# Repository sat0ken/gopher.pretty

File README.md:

# gopher.pretty

Gopher kicad Footprint Library.
Let's make your own Gopher Board, and enjoy tinygo!

## Usage

1. clone this repository to your pc.
2. Add the cloned folder to the footprint library path of kicad.
3. make your own board!

You can also use this as is.

I have confirmed that the project can be opened using kicad 8.0.

The Kicad project I created can be found in the following repository.

[https://github.com/sat0ken/gopher-board](https://github.com/sat0ken/gopher-board)

## Thanks

The Go gopher was designed by Renee French.
[http://reneefrench.blogspot.com/](http://reneefrench.blogspot.com/)

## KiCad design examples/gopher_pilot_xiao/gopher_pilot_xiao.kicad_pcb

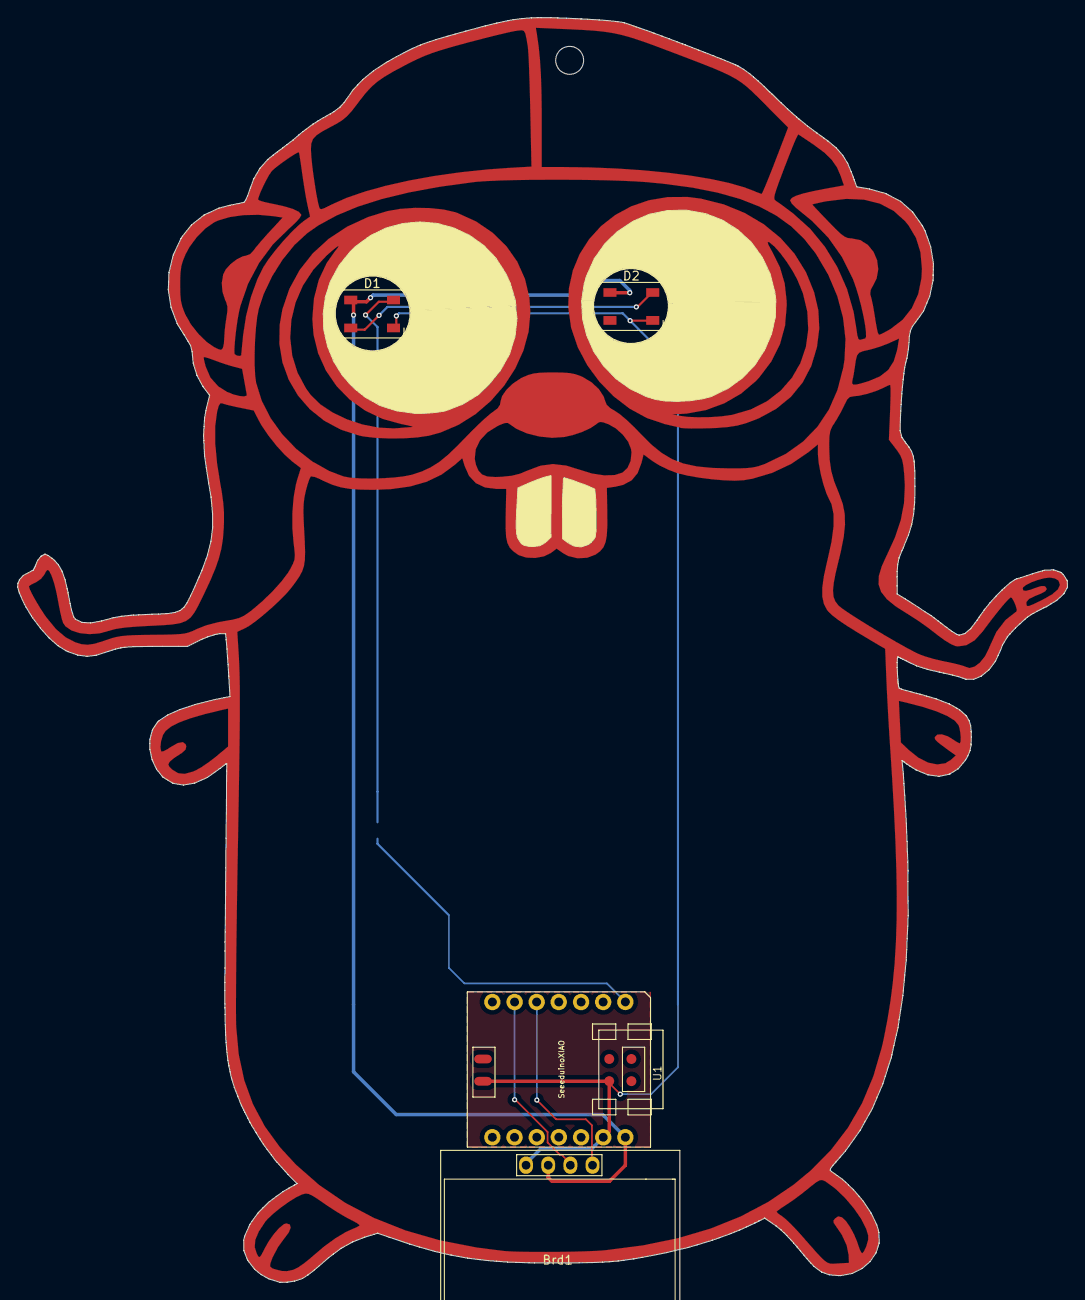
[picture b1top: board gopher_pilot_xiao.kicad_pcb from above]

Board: 2 copper layers, 120.3 x 144.9 mm, 5 parts (1 on the bottom side), 7 nets.

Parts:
Brd1: SSD1306; 128x64OLED
D1, D2: WS2812B; LED_WS2812B_PLCC4_5.0x5.0mm_P3.2mm
R2: 330; R_0805_2012Metric
U1: SeeeduinoXIAO; Seeeduino XIAO-MOUDLE14P-2.54-21X17.8MM_PinSocket

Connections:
/PA02: R2.1, U1.1
GND: Brd1.1, D1.3, D2.3, U1.13, U1.16, U1.20
unnamed: Brd1.3, U1.6
unnamed: Brd1.4, U1.5
unnamed: D1.2, D2.4
unnamed: D1.4, R2.2
VCC: Brd1.2, D1.1, D2.1, U1.14, U1.15

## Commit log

2024-08-27 add files
2024-08-29 update example
2024-09-22 move example to other repository
2024-09-22 move file to top dir
